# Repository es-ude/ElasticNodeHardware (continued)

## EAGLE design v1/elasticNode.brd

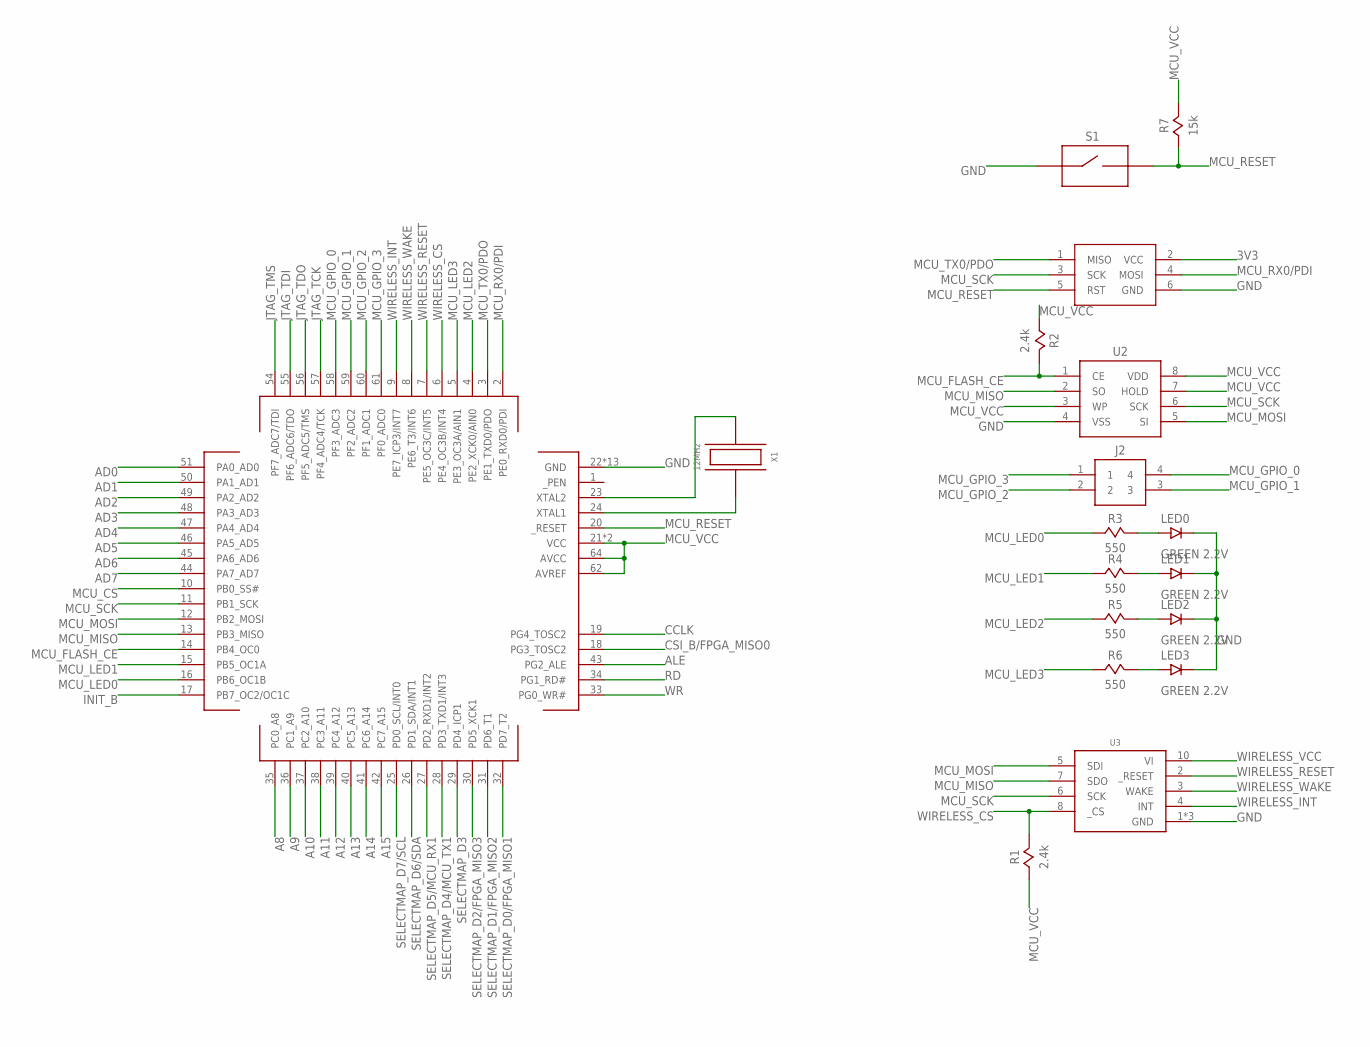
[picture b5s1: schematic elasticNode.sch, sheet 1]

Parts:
J1: ISP_CONN_6PIN; 3X2_HEADER_SMT
J2: FEMALE_HEADER_2X2; 2X2_HEADER
LED0, LED1, LED2, LED3: GREEN 2.2V; 0805
R1, R2: 2.4k; 0805
R3, R4, R5, R6: 550; 0805
R7: 15k; 0805
S1: SPST_BUTTON2PIN_SMT; SPST_2PIN_SMT
U1: ATMEGA64AQFN; QFN64
U2: SST26VF032B; SOIC8
U3: MRF24J40MA
X1: 12MHz; 3.2X2.5_OSC

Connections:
3V3: J1.2 (VCC); also elsewhere on the board
A8: U1.35 (PC0_A8); also elsewhere on the board
A9: U1.36 (PC1_A9); also elsewhere on the board
A10: U1.37 (PC2_A10); also elsewhere on the board
A11: U1.38 (PC3_A11); also elsewhere on the board
A12: U1.39 (PC4_A12); also elsewhere on the board
A13: U1.40 (PC5_A13); also elsewhere on the board
A14: U1.41 (PC6_A14); also elsewhere on the board
A15: U1.42 (PC7_A15); also elsewhere on the board
AD0: U1.51 (PA0_AD0); also elsewhere on the board
AD1: U1.50 (PA1_AD1); also elsewhere on the board
AD2: U1.49 (PA2_AD2); also elsewhere on the board
AD3: U1.48 (PA3_AD3); also elsewhere on the board
AD4: U1.47 (PA4_AD4); also elsewhere on the board
AD5: U1.46 (PA5_AD5); also elsewhere on the board
AD6: U1.45 (PA6_AD6); also elsewhere on the board
AD7: U1.44 (PA7_AD7); also elsewhere on the board
ALE: U1.43 (PG2_ALE); also elsewhere on the board
CCLK: U1.19 (PG4_TOSC2); also elsewhere on the board
CSI_B/FPGA_MISO0: U1.18 (PG3_TOSC2); also elsewhere on the board
GND: J1.6 (GND), LED0.2, LED1.2, LED2.2, LED3.2, S1.1, U1.22 (GND), U1.53 (GND), U1.63 (GND), U1.PAD (GND), U1.VIA1 (GND), U1.VIA2 (GND), U1.VIA3 (GND), U1.VIA4 (GND), U1.VIA5 (GND), U1.VIA6 (GND), U1.VIA7 (GND), U1.VIA8 (GND), U1.VIA9 (GND), U2.4 (VSS), U3.1 (GND), U3.11 (GND), U3.12 (GND); also elsewhere on the board
INIT_B: U1.17 (PB7_OC2/OC1C); also elsewhere on the board
JTAG_TCK: U1.57 (PF4_ADC4/TCK); also elsewhere on the board
JTAG_TDI: U1.55 (PF6_ADC6/TDO); also elsewhere on the board
JTAG_TDO: U1.56 (PF5_ADC5/TMS); also elsewhere on the board
JTAG_TMS: U1.54 (PF7_ADC7/TDI); also elsewhere on the board
MCU_CS: U1.10 (PB0_SS#)
MCU_FLASH_CE: R2.2, U1.14 (PB4_OC0), U2.1 (CE)
MCU_GPIO_0: J2.4, U1.58 (PF3_ADC3)
MCU_GPIO_1: J2.3, U1.59 (PF2_ADC2)
MCU_GPIO_2: J2.2, U1.60 (PF1_ADC1)
MCU_GPIO_3: J2.1, U1.61 (PF0_ADC0)
MCU_LED0: R3.1, U1.16 (PB6_OC1B)
MCU_LED1: R4.1, U1.15 (PB5_OC1A)
MCU_LED2: R5.1, U1.4 (PE2_XCK0/AIN0)
MCU_LED3: R6.1, U1.5 (PE3_OC3A/AIN1)
MCU_MISO: U1.13 (PB3_MISO), U2.2 (SO), U3.7 (SDO)
MCU_MOSI: U1.12 (PB2_MOSI), U2.5 (SI), U3.5 (SDI)
MCU_RESET: J1.5 (RST), R7.1, S1.2 (3), U1.20 (_RESET)
MCU_RX0/PDI: J1.4 (MOSI), U1.2 (PE0_RXD0/PDI); also elsewhere on the board
MCU_SCK: J1.3 (SCK), U1.11 (PB1_SCK), U2.6 (SCK), U3.6 (SCK)
MCU_TX0/PDO: J1.1 (MISO), U1.3 (PE1_TXD0/PDO); also elsewhere on the board
MCU_VCC: R1.1, R2.1, R7.2, U1.21 (VCC), U1.52 (VCC), U1.62 (AVREF), U1.64 (AVCC), U2.3 (WP), U2.7 (HOLD), U2.8 (VDD); also elsewhere on the board
unnamed: LED3.1, R6.2
unnamed: LED2.1, R5.2
unnamed: LED1.1, R4.2
unnamed: LED0.1, R3.2
unnamed: U1.23 (XTAL2), X1.2
unnamed: U1.24 (XTAL1), X1.4
RD: U1.34 (PG1_RD#); also elsewhere on the board
SELECTMAP_D0/FPGA_MISO1: U1.32 (PD7_T2); also elsewhere on the board
SELECTMAP_D1/FPGA_MISO2: U1.31 (PD6_T1); also elsewhere on the board
SELECTMAP_D2/FPGA_MISO3: U1.30 (PD5_XCK1); also elsewhere on the board
SELECTMAP_D3: U1.29 (PD4_ICP1); also elsewhere on the board
SELECTMAP_D4/MCU_TX1: U1.28 (PD3_TXD1/INT3); also elsewhere on the board
SELECTMAP_D5/MCU_RX1: U1.27 (PD2_RXD1/INT2); also elsewhere on the board
SELECTMAP_D6/SDA: U1.26 (PD1_SDA/INT1); also elsewhere on the board
SELECTMAP_D7/SCL: U1.25 (PD0_SCL/INT0); also elsewhere on the board
WIRELESS_CS: R1.2, U1.6 (PE4_OC3B/INT4), U3.8 (_CS)
WIRELESS_INT: U1.9 (PE7_ICP3/INT7), U3.4 (INT)
WIRELESS_RESET: U1.7 (PE5_OC3C/INT5), U3.2 (_RESET)
WIRELESS_VCC: U3.10 (VI); also elsewhere on the board
WIRELESS_WAKE: U1.8 (PE6_T3/INT6), U3.3 (WAKE)
WR: U1.33 (PG0_WR#); also elsewhere on the board

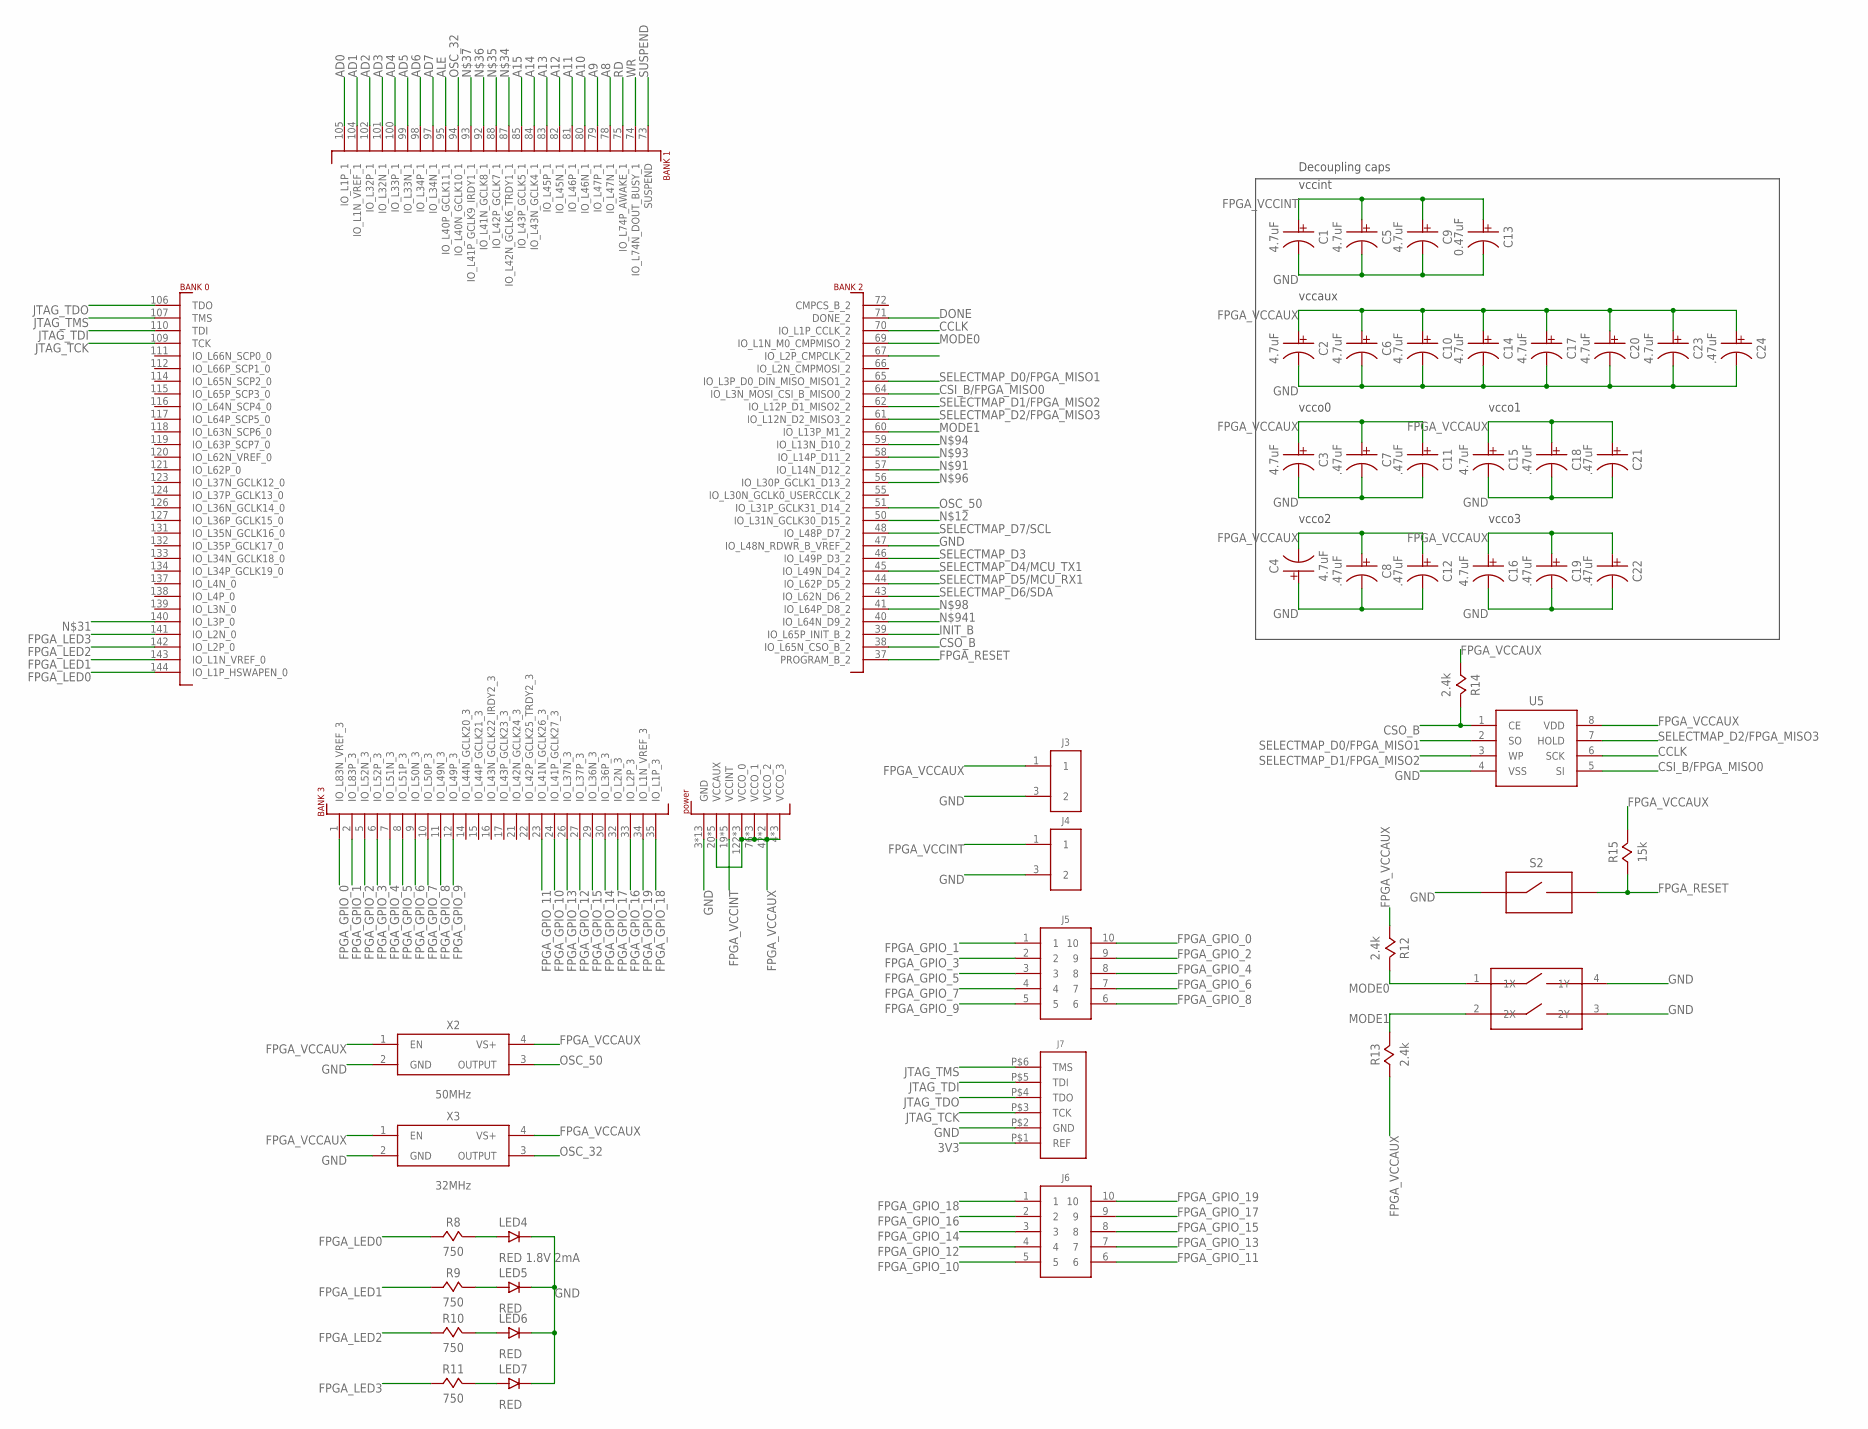
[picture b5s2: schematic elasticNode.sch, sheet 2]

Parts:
C1, C2, C3, C4, C5, C6, C9, C10, C14, C15, C16, C17, C20, C23: 4.7uF; 0805
C7, C8, C11, C12, C18, C19, C21, C22: .47uF; 0402
C13: 0.47uF; 0402
C24: .47uF; 0805
J3, J4: FEMALE_HEADER_2X1; 2X1_HEADER
J5, J6: FEMALE_HEADER_5X2; 5X2_HEADER
J7: JTAG_CONN_6PINTHT; 6X1_HEADER
LED4: RED 1.8V 2mA; 0805
LED5, LED6, LED7: RED; 0805
R8, R9, R10, R11: 750; 0805
R12, R13, R14: 2.4k; 0805
R15: 15k; 0805
S2: SPST_BUTTON2PIN_SMT; SPST_2PIN_SMT
S3: SPST_DIP_2SMT; SPST_DIP2_SMT
U4: SPARTAN6-LX9; TQG144
U5: SST26VF032B; SOIC8
X2: 50MHz; 3.2X2.5_OSC
X3: 32MHz; 3.2X2.5_OSC

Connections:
3V3: J7.P$1 (REF); also elsewhere on the board
A8: U4.78 (IO_L47N_1); also elsewhere on the board
A9: U4.79 (IO_L47P_1); also elsewhere on the board
A10: U4.80 (IO_L46N_1); also elsewhere on the board
A11: U4.81 (IO_L46P_1); also elsewhere on the board
A12: U4.82 (IO_L45N_1); also elsewhere on the board
A13: U4.83 (IO_L45P_1); also elsewhere on the board
A14: U4.84 (IO_L43N_GCLK4_1); also elsewhere on the board
A15: U4.85 (IO_L43P_GCLK5_1); also elsewhere on the board
AD0: U4.105 (IO_L1P_1); also elsewhere on the board
AD1: U4.104 (IO_L1N_VREF_1); also elsewhere on the board
AD2: U4.102 (IO_L32P_1); also elsewhere on the board
AD3: U4.101 (IO_L32N_1); also elsewhere on the board
AD4: U4.100 (IO_L33P_1); also elsewhere on the board
AD5: U4.99 (IO_L33N_1); also elsewhere on the board
AD6: U4.98 (IO_L34P_1); also elsewhere on the board
AD7: U4.97 (IO_L34N_1); also elsewhere on the board
ALE: U4.95 (IO_L40P_GCLK11_1); also elsewhere on the board
CCLK: U4.70 (IO_L1P_CCLK_2), U5.6 (SCK); also elsewhere on the board
CSI_B/FPGA_MISO0: U4.64 (IO_L3N_MOSI_CSI_B_MISO0_2), U5.5 (SI); also elsewhere on the board
CSO_B: R14.2, U4.38 (IO_L65N_CSO_B_2), U5.1 (CE)
DONE: U4.71 (DONE_2)
FPGA_GPIO_0: J5.10, U4.1 (IO_L83N_VREF_3)
FPGA_GPIO_1: J5.1, U4.2 (IO_L83P_3)
FPGA_GPIO_2: J5.9, U4.5 (IO_L52N_3)
FPGA_GPIO_3: J5.2, U4.6 (IO_L52P_3)
FPGA_GPIO_4: J5.8, U4.7 (IO_L51N_3)
FPGA_GPIO_5: J5.3, U4.8 (IO_L51P_3)
FPGA_GPIO_6: J5.7, U4.9 (IO_L50N_3)
FPGA_GPIO_7: J5.4, U4.10 (IO_L50P_3)
FPGA_GPIO_8: J5.6, U4.11 (IO_L49N_3)
FPGA_GPIO_9: J5.5, U4.12 (IO_L49P_3)
FPGA_GPIO_10: J6.5, U4.24 (IO_L41P_GCLK27_3)
FPGA_GPIO_11: J6.6, U4.23 (IO_L41N_GCLK26_3)
FPGA_GPIO_12: J6.4, U4.27 (IO_L37P_3)
FPGA_GPIO_13: J6.7, U4.26 (IO_L37N_3)
FPGA_GPIO_14: J6.3, U4.30 (IO_L36P_3)
FPGA_GPIO_15: J6.8, U4.29 (IO_L36N_3)
FPGA_GPIO_16: J6.2, U4.33 (IO_L2P_3)
FPGA_GPIO_17: J6.9, U4.32 (IO_L2N_3)
FPGA_GPIO_18: J6.1, U4.35 (IO_L1P_3)
FPGA_GPIO_19: J6.10, U4.34 (IO_L1N_VREF_3)
FPGA_LED0: R8.1, U4.144 (IO_L1P_HSWAPEN_0)
FPGA_LED1: R9.1, U4.143 (IO_L1N_VREF_0)
FPGA_LED2: R10.1, U4.142 (IO_L2P_0)
FPGA_LED3: R11.1, U4.141 (IO_L2N_0)
FPGA_RESET: R15.1, S2.2 (3), U4.37 (PROGRAM_B_2)
FPGA_VCCAUX: C2.1, C3.1, C4.2, C6.1, C7.1, C8.1, C10.1, C11.1, C12.1, C14.1, C15.1, C16.1, C17.1, C18.1, C19.1, C20.1, C21.1, C22.1, C23.1, C24.1, J3.1, R12.1, R13.1, R14.1, R15.2, U4.4 (VCCO_3), U4.18 (VCCO_3), U4.20 (VCCAUX), U4.31 (VCCO_3), U4.36 (VCCAUX), U4.42 (VCCO_2), U4.53 (VCCAUX), U4.63 (VCCO_2), U4.76 (VCCO_1), U4.86 (VCCO_1), U4.90 (VCCAUX), U4.103 (VCCO_1), U4.122 (VCCO_0), U4.125 (VCCO_0), U4.129 (VCCAUX), U4.135 (VCCO_0), U5.8 (VDD), X2.1 (EN), X2.4 (VS+), X3.1 (EN), X3.4 (VS+); also elsewhere on the board
FPGA_VCCINT: C1.1, C5.1, C9.1, C13.1, J4.1, U4.19 (VCCINT), U4.28 (VCCINT), U4.52 (VCCINT), U4.89 (VCCINT), U4.128 (VCCINT); also elsewhere on the board
GND: C1.2, C2.2, C3.2, C4.1, C5.2, C6.2, C7.2, C8.2, C9.2, C10.2, C11.2, C12.2, C13.2, C14.2, C15.2, C16.2, C17.2, C18.2, C19.2, C20.2, C21.2, C22.2, C23.2, C24.2, J3.3 (2), J4.3 (2), J7.P$2 (GND), LED4.2, LED5.2, LED6.2, LED7.2, S2.1, S3.3 (2Y), S3.4 (1Y), U4.3 (GND), U4.13 (GND), U4.25 (GND), U4.47 (IO_L48N_RDWR_B_VREF_2), U4.49 (GND), U4.54 (GND), U4.68 (GND), U4.77 (GND), U4.91 (GND), U4.96 (GND), U4.108 (GND), U4.113 (GND), U4.130 (GND), U4.136 (GND), U5.4 (VSS), X2.2 (GND), X3.2 (GND); also elsewhere on the board
INIT_B: U4.39 (IO_L65P_INIT_B_2); also elsewhere on the board
JTAG_TCK: J7.P$3 (TCK), U4.109 (TCK); also elsewhere on the board
JTAG_TDI: J7.P$5 (TDI), U4.110 (TDI); also elsewhere on the board
JTAG_TDO: J7.P$4 (TDO), U4.106 (TDO); also elsewhere on the board
JTAG_TMS: J7.P$6 (TMS), U4.107 (TMS); also elsewhere on the board
MODE0: R12.2, S3.1 (1X), U4.69 (IO_L1N_M0_CMPMISO_2)
MODE1: R13.2, S3.2 (2X), U4.60 (IO_L13P_M1_2)
unnamed: LED7.1, R11.2
unnamed: LED6.1, R10.2
unnamed: LED5.1, R9.2
unnamed: LED4.1, R8.2
OSC_32: U4.94 (IO_L40N_GCLK10_1), X3.3 (OUTPUT)
OSC_50: U4.51 (IO_L31P_GCLK31_D14_2), X2.3 (OUTPUT)
RD: U4.75 (IO_L74P_AWAKE_1); also elsewhere on the board
SELECTMAP_D0/FPGA_MISO1: U4.65 (IO_L3P_D0_DIN_MISO_MISO1_2), U5.2 (SO); also elsewhere on the board
SELECTMAP_D1/FPGA_MISO2: U4.62 (IO_L12P_D1_MISO2_2), U5.3 (WP); also elsewhere on the board
SELECTMAP_D2/FPGA_MISO3: U4.61 (IO_L12N_D2_MISO3_2), U5.7 (HOLD); also elsewhere on the board
SELECTMAP_D3: U4.46 (IO_L49P_D3_2); also elsewhere on the board
SELECTMAP_D4/MCU_TX1: U4.45 (IO_L49N_D4_2); also elsewhere on the board
SELECTMAP_D5/MCU_RX1: U4.44 (IO_L62P_D5_2); also elsewhere on the board
SELECTMAP_D6/SDA: U4.43 (IO_L62N_D6_2); also elsewhere on the board
SELECTMAP_D7/SCL: U4.48 (IO_L48P_D7_2); also elsewhere on the board
SUSPEND: U4.73 (SUSPEND)
WR: U4.74 (IO_L74N_DOUT_BUSY_1); also elsewhere on the board

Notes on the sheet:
Decoupling caps
vccint
vccaux
vcco0
vcco1
vcco2
vcco3

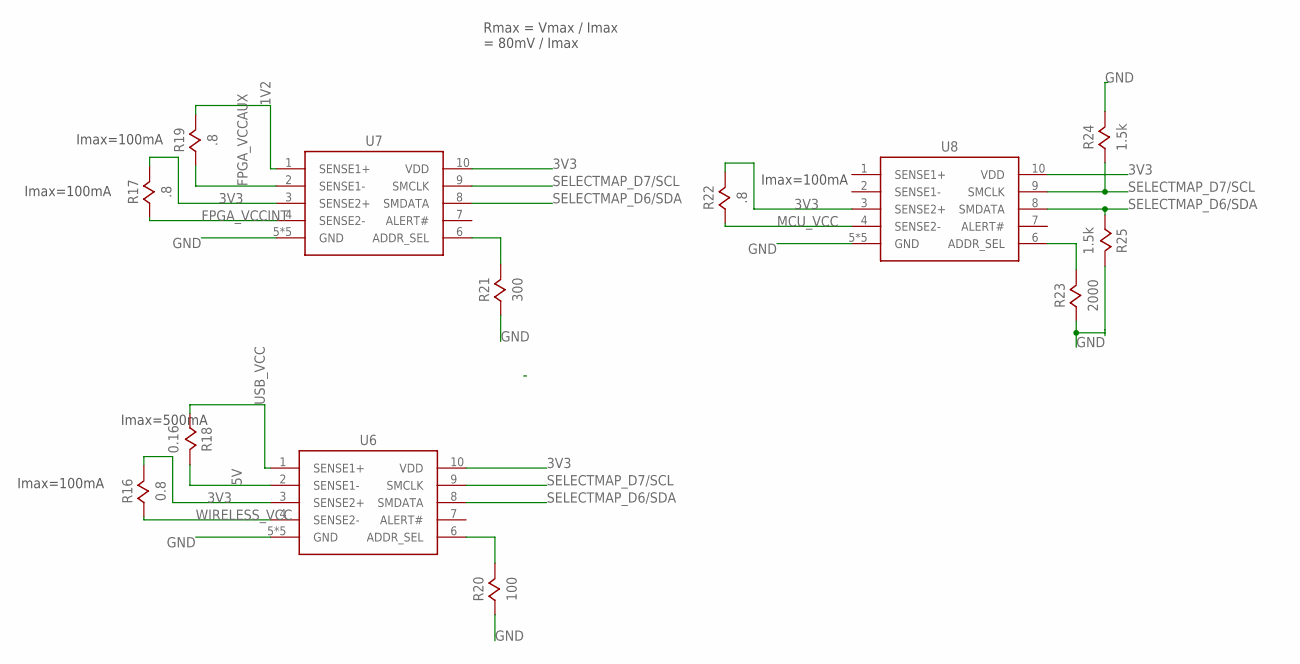
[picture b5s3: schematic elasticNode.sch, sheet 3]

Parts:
R16: 0.8; 0805
R17, R19, R22: .8; 0805
R18: 0.16; 0805
R20: 100; 0805
R21: 300; 0805
R23: 2000; 0805
R24, R25: 1.5k; 0805
U6, U7, U8: PAC1720; VDFN10

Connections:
1V2: R19.2, U7.1 (SENSE1+); also elsewhere on the board
3V3: R16.2, R17.2, R22.2, U6.3 (SENSE2+), U6.10 (VDD), U7.3 (SENSE2+), U7.10 (VDD), U8.3 (SENSE2+), U8.10 (VDD); also elsewhere on the board
5V: R18.2, U6.2 (SENSE1-); also elsewhere on the board
FPGA_VCCAUX: R19.1, U7.2 (SENSE1-); also elsewhere on the board
FPGA_VCCINT: R17.1, U7.4 (SENSE2-); also elsewhere on the board
GND: R20.1, R21.1, R23.1, R24.2, U6.5 (GND), U6.P$1 (GND), U6.P$2 (GND), U6.P$3 (GND), U6.P$4 (GND), U7.5 (GND), U7.P$1 (GND), U7.P$2 (GND), U7.P$3 (GND), U7.P$4 (GND), U8.5 (GND), U8.P$1 (GND), U8.P$2 (GND), U8.P$3 (GND), U8.P$4 (GND); also elsewhere on the board
MCU_VCC: R22.1, U8.4 (SENSE2-); also elsewhere on the board
unnamed: R23.2, U8.6 (ADDR_SEL)
unnamed: R21.2, U7.6 (ADDR_SEL)
unnamed: R20.2, U6.6 (ADDR_SEL)
SELECTMAP_D6/SDA: R25.1, U6.8 (SMDATA), U7.8 (SMDATA), U8.8 (SMDATA); also elsewhere on the board
SELECTMAP_D7/SCL: R24.1, U6.9 (SMCLK), U7.9 (SMCLK), U8.9 (SMCLK); also elsewhere on the board
USB_VCC: R18.1, U6.1 (SENSE1+); also elsewhere on the board
WIRELESS_VCC: R16.1, U6.4 (SENSE2-); also elsewhere on the board

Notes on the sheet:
Rmax = Vmax / Imax = 80mV / Imax
Imax=100mA
Imax=500mA

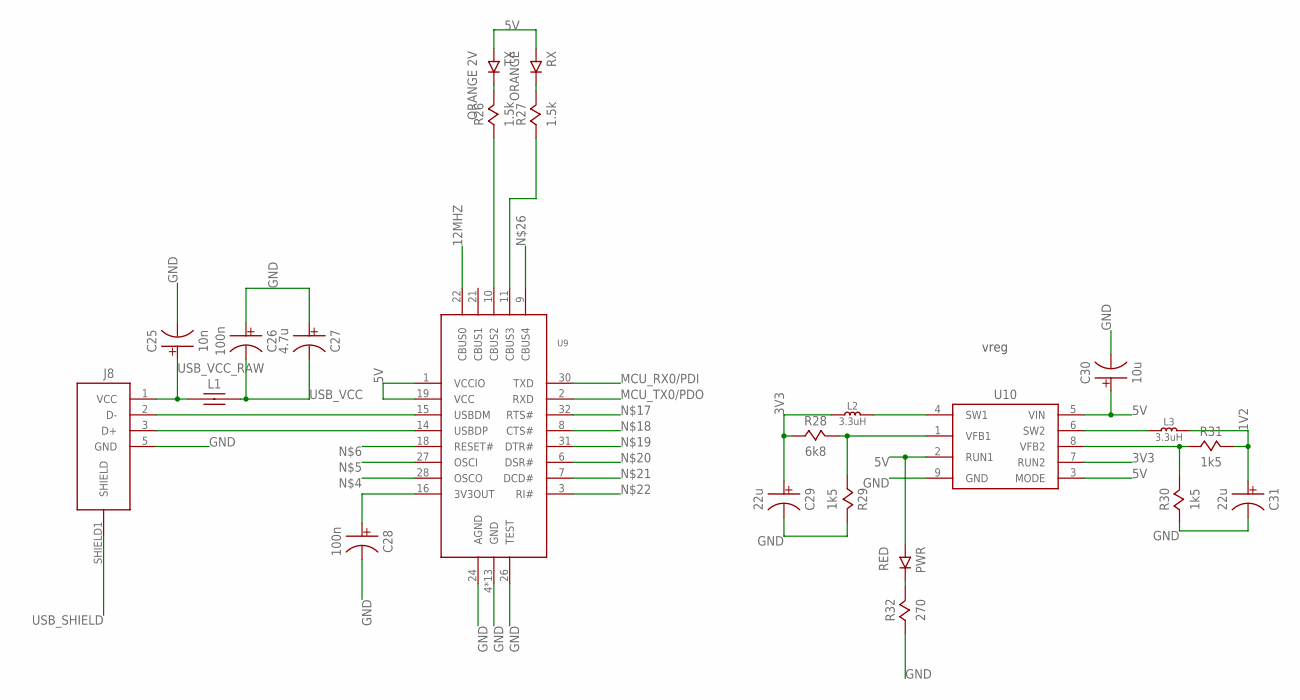
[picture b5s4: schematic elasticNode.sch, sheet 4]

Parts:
C25: 10n; 0805
C26, C28: 100n; 0805
C27: 4.7u; 0805
C29, C31: 22u; 0805
C30: 10u; 0805
J8: USB_CONN; USB_MICRO_B
L1: 40Ohm 1.5A; 0805
L2, L3: 3.3uH; 0805
PWR: RED; 0805
R26, R27: 1.5k; 0805
R28: 6k8; 0805
R29, R30, R31: 1k5; 0805
R32: 270; 0805
RX: ORANGE; 0805
TX: ORANGE 2V; 0805
U9: FT232R; QFN32
U10: LTC3419DFN; DFN8

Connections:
1V2: C31.1, L3.2, R31.2; also elsewhere on the board
3V3: C29.1, L2.1, R28.1, U10.7 (RUN2); also elsewhere on the board
5V: C30.1, PWR.1, RX.1, TX.1, U9.1 (VCCIO), U9.19 (VCC), U10.2 (RUN1), U10.3 (MODE), U10.5 (VIN); also elsewhere on the board
12MHZ: U9.22 (CBUS0)
FTDI_RXLED: R27.1, U9.11 (CBUS3)
GND: C25.2, C26.1, C27.1, C28.2, C29.2, C30.2, C31.2, J8.5 (GND), R29.2, R30.1, R32.1, U9.4 (GND), U9.17 (GND), U9.20 (GND), U9.24 (AGND), U9.26 (TEST), U9.33 (GND), U9.P$1 (GND), U9.P$2 (GND), U9.P$3 (GND), U9.P$4 (GND), U9.P$5 (GND), U9.P$6 (GND), U9.P$7 (GND), U9.P$8 (GND), U9.P$9 (GND), U10.9 (GND); also elsewhere on the board
MCU_RX0/PDI: U9.30 (TXD); also elsewhere on the board
MCU_TX0/PDO: U9.2 (RXD); also elsewhere on the board
unnamed: L2.2, U10.4 (SW1)
unnamed: R28.2, R29.1, U10.1 (VFB1)
unnamed: C28.1, U9.16 (3V3OUT)
unnamed: R30.2, R31.1, U10.8 (VFB2)
unnamed: L3.1, U10.6 (SW2)
unnamed: R26.1, U9.10 (CBUS2)
unnamed: R26.2, TX.2
unnamed: R27.2, RX.2
unnamed: PWR.2, R32.2
USBD+: J8.3 (D+), U9.14 (USBDP)
USBD-: J8.2 (D-), U9.15 (USBDM)
USB_SHIELD: J8.SHIELD1 (SHIELD)
USB_VCC: C26.2, C27.2, L1.2; also elsewhere on the board
USB_VCC_RAW: C25.1, J8.1 (VCC), L1.1

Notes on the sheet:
vreg

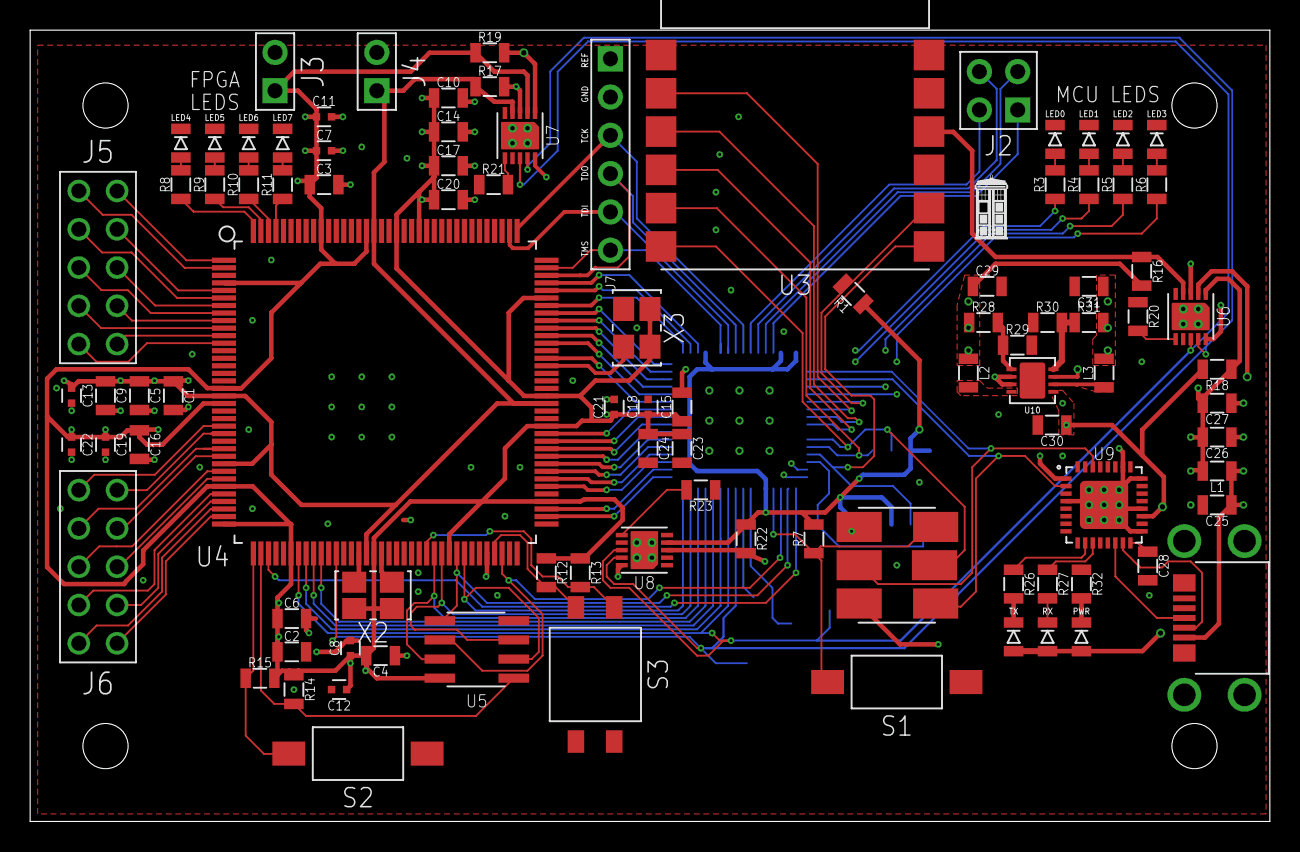
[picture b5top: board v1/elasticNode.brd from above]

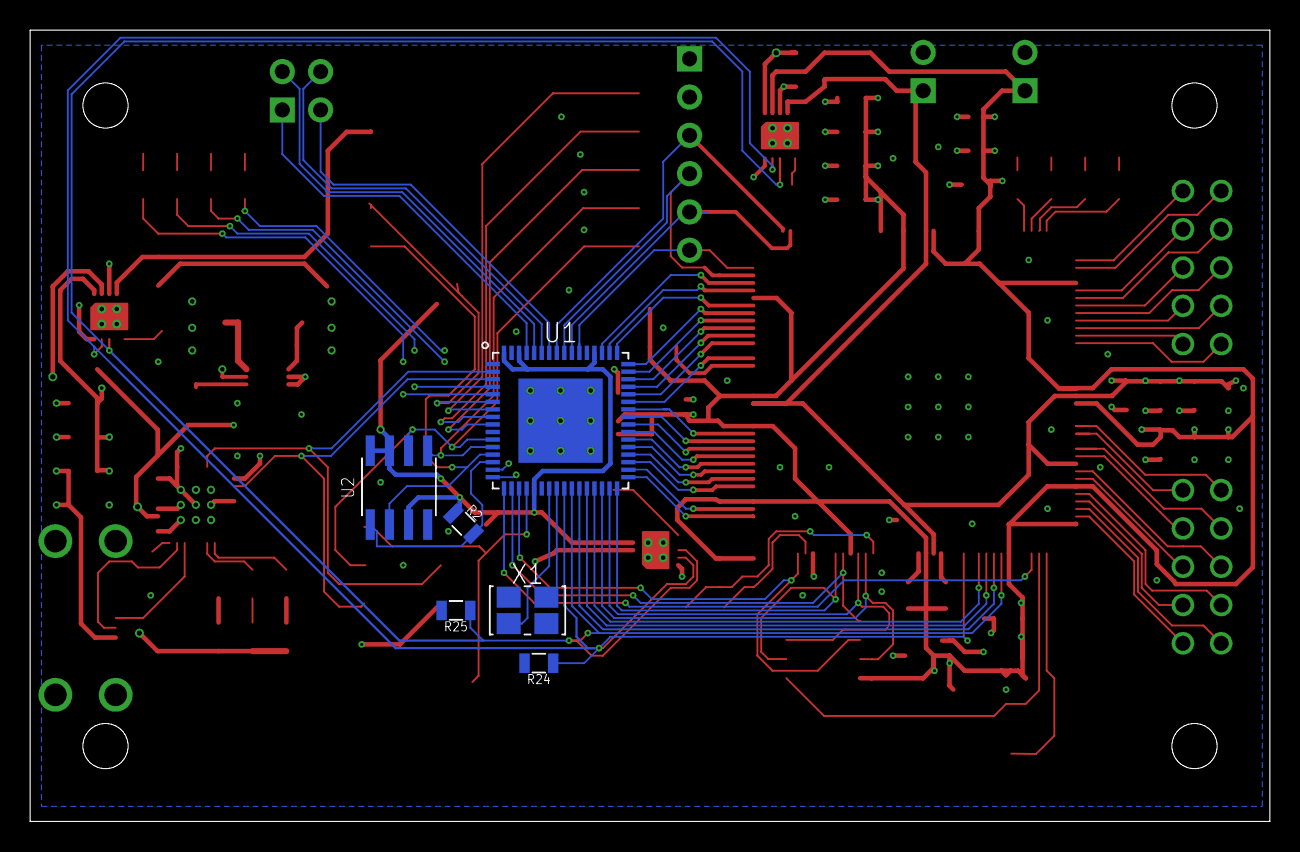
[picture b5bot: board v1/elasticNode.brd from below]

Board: 4 copper layers, 82.2 x 52.5 mm, 101 parts (6 on the bottom side), 118 nets.

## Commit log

2017-05-01 initial design partly sch
2017-05-02 working on elastic node
2017-05-02 removed jobs
2017-05-02 small edits
2017-05-07 home working on elastic node
2017-05-09 small routing at home
2017-05-10 lots of routing, and reorganising
2017-05-10 small home edits
2017-05-16 lots of routing, removed latch
2017-05-17 added another measurement
2017-05-17 changed to single power plane
2017-05-18 finished first round rerouting
2017-05-22 small edits before unified
2017-07-28 last before fixes to v2
2017-08-04 changed i2c to pullup
2017-08-04 updated board for previous pullups and swapped fpga power rails
2017-08-04 added smd usb connector
2017-08-05 updated footprints, moved reset buttons, general reorganising
2017-10-21 first part toward separate monitoring board
2017-10-23 backup of v2
2017-10-31 first part of new layout
2017-11-01 New layout is done
2017-11-02 elasticnode mostly finished with smaller footprint
2017-11-03 4-switch dip added into design
2017-11-06 also monitoring PAC1720 current
2017-11-21 small changes for mosfet power
2017-12-06 added fpga_power control line, some text and minor changes to layout
2019-01-03 partial v3
2019-03-07 information collected, and documentations for records.
2019-03-08 Remove old MCU
    working on the mother board interface.
2019-03-11 backup before review
2019-03-13 back up before review.
2019-03-13 Layout work start.
2019-03-16 backup
2019-03-16 backup
    SRAM and FPGA finished, now connecting fpga and MCU
2019-03-17 back up
    spi_sck didn’t connect to FPGA,OK？
2019-03-17 backup
    SPI FLASH ok.
2019-03-19 backup
    FPGA_GPIO connecting
2019-03-21 back up
    power line need check again.
2019-03-22 only daughter board interface left
2019-03-24 finish the work.
2019-03-25 Fix DRC errors.
2019-03-25 Fixed all DRC Errors and Warnings.
2019-03-25 move back the logo
2019-03-26 add the direction for the mother board interface.
2019-03-26 backup before renumber the elements.
2019-03-26 Add JTAG Header
    Checked the schematic diagram again.
2019-03-26 renumber all elements.
2019-03-26 Add a new version, v4.
2019-03-26 Change the capacitors’ name positions.
2019-03-26 ready for ordering.
2019-03-26 fix mistake about the capacitor of 4.7uF
2019-03-28 Change the 100M clock signals connection
    Add enable signal to oscillator 100M, and check aux IOs Voltage.
2019-03-29 changed the position of the little notch
2019-04-25 Modified the footprint of the FPGA and MCU.
    Rechecked the board again.
2019-06-30 Optimized the distance between the elements.
2019-07-03 Fixed some errors check.
2019-11-17 add the v4 with dual port ram.
2020-07-07 clean files.
2023-01-30 add env5 stuff
2023-01-30 fix super link
2023-01-30 fix extension board schematic link
2023-02-13 esp-at build guide
2023-02-13 esp-at add prebuild firmware
2023-02-13 modify readme
2023-02-13 modify readme fix link
2023-02-14 add both firmware
2023-04-26 some documents for troubleshot
2023-07-03 version stared
2023-07-17 change vias position
2023-08-30 point ordered PCBA from JLCPCB
2023-08-30 point ordered PCBA from JLCPCB for the mainboard
2023-10-24 optimize design half done
2023-10-24 changed a resistor value
2023-10-27 fixed the voltage regulator
2023-10-27 changed the direction of battery connector
2023-10-27 prepared CAM files
2024-07-18 Create LICENSE
